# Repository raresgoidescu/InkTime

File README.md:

<!-- Copyright GOIDESCU Rareș-Ștefan 2026 -->

# InkTime

InkTime is a proper solution for the people that can't be bothered to charge their watch daily. This is a beginner's attempt at implementing it. Please see [the disclaimer and the license](#trademark-disclaimer) notice.

## Block Diagram

## Bill of Materials

| Part / Value | Refs | Qty | Procurement | Datasheet |
| :--- | :--- | :---: | :--- | :--- |
| **Active ICs & Semiconductors** | | | | |
| nRF52840-QFAA Microcontroller | U1 | 1 | [DigiKey](https://www.digikey.be/en/products/detail/nordic-semiconductor-asa/NRF52840-QFAA-F-R/15929812) | [DS](https://www.nordicsemi.com/Products/nRF52840) |
| BMA423 Triaxial Accelerometer | IC3 | 1 |[Mouser 262-BMA423](https://eu.mouser.com/ProductDetail/Bosch-Sensortec/BMA423?qs=HXFqYaX1Q2xC%252BSgeGoX3mg%3D%3D) | [DS](https://watchy.sqfmi.com/assets/files/BST-BMA423-DS000-1509600-950150f51058597a6234dd3eaafbb1f0.pdf) |
| BQ25180YBGR Li-Ion Charger | IC1 | 1 |[Mouser 595-BQ25180YBGR](https://eu.mouser.com/ProductDetail/Texas-Instruments/BQ25180YBGR?qs=doiCPypUmgEWjAK%252BJAX6Tw%3D%3D) | [DS](https://www.ti.com/product/BQ25180) |
| DRV2605YZFR Haptic Driver | IC2 | 1 | [Mouser](https://eu.mouser.com/ProductDetail/Texas-Instruments/DRV2605YZFR?qs=9Zb5cNRUa0Ym539PjgFm3g%3D%3D) | [DS](https://www.ti.com/product/DRV2605) |
| MAX17048G+T10 Fuel Gauge | U3 | 1 | [DigiKey](https://www.digikey.com/en/products/detail/analog-devices-inc-maxim-integrated/MAX17048G-T10/3758921) | [DS](https://www.analog.com/en/products/max17048.html) |
| RT6160AWSC Buck-Boost DC-DC | IC9 | 1 |[Mouser 835-RT6160AWSC](https://eu.mouser.com/ProductDetail/Richtek/RT6160AWSC?qs=amGC7iS6iy%2FLd9PSoixZXQ%3D%3D) | [DS](https://www.richtek.com/Products/Switching%20Regulators/Buck-Boost%20Converter/RT6160A) |
| USBLC6-2SC6Y ESD Protection | D3 | 1 | [DigiKey](https://www.digikey.com/en/products/detail/stmicroelectronics/USBLC6-2SC6Y/2819177) | [DS](https://www.st.com/en/protections-and-emi-filters/usblc6-2.html) |
| MBR0530 Schottky Diode | D2, D4, D5 | 3 | [Mouser](https://eu.mouser.com/c/semiconductors/discrete-semiconductors/diodes-rectifiers/schottky-diodes-rectifiers/?m=onsemi&series=MBR0530) | [DS](https://www.onsemi.com/pdf/datasheet/mbr0530t1-d.pdf) |
| DMG2305UX-7 P-CH MOSFET 20V/4.2A | Q1 | 1 | [Mouser](https://ro.mouser.com/ProductDetail/Diodes-Incorporated/DMG2305UX-7?qs=L1DZKBg7t5F%2FNBHrjfxC%252Bg%3D%3D) | [DS](https://www.diodes.com/assets/Datasheets/DMG2305UX.pdf) |
| SI1308EDL-T1-GE3 N-CH MOSFET 30V/1.5A | Q3 | 1 | [Mouser](https://eu.mouser.com/ProductDetail/Vishay-Semiconductors/SI1308EDL-T1-GE3?qs=bX1%252BNvsK%2FBramh9tgpOaEw%3D%3D) |[DS](https://www.vishay.com/docs/63399/si1308edl.pdf) |
| **Connectors & Electromechanical** | | | | |
| 2450AT18B100E 2.45 GHz Antenna | ANT1 | 1 | [Mouser 609-2450AT18B100E](https://www.mouser.co.uk/ProductDetail/Johanson-Technology/2450AT18B100E?qs=yCnrNFeXz%252Bh5MFsFIXGZGA%3D%3D) | [DS](https://www.johansontechnology.com/datasheets/2450AT18B100/2450AT18B100.pdf) |
| 503480-2400 24-pin FPC 0.5 mm | J1 | 1 |[Mouser 538-503480-2400](https://eu.mouser.com/ProductDetail/Molex/503480-2400?qs=OAhjpuo3Vu7efIoxFh9AOw%3D%3D) | [DS](https://www.molex.com/en-us/products/part-detail/5034802400?display=pdf) |
| KH-TYPE-C-16P USB Type-C 16-pin | J4 | 1 | [xonelec.com](https://www.xonelec.com/mpn/kinghelm/khtypec16p) | [DS](https://xonstorage.z8.web.core.windows.net/pdf/kinghelm_khtypec16p_xonjuly20_20_link.pdf) |
| TC2030-IDC 6-pin Debug Adapter | J2 | 1 | [Tag-Connect](https://www.tag-connect.com/product/tc2030-idc-6-pin-tag-connect-plug-of-nails-spring-pin-cable-with-legs) | [DS](https://www.tag-connect.com/wp-content/uploads/bsk-pdf-manager/2019/12/TC2030-IDC-Datasheet-Rev-B.pdf) |
| EVP-AKE31A Tactile Button | SW_DN, SW_ENT, SW_UP | 3 |[Mouser](https://eu.mouser.com/ProductDetail/Panasonic/EVP-AKE31A?qs=EU6FO9ffTwe%252BJzX5LvvHqA%3D%3D) | [DS](https://www.tme.eu/Document/7d6137f818fadb8daa876cedb29b6731/EVPAKseries.pdf) |
| **Inductors** | | | | |
| FTC252012SR47MBCA 0.47 µH | L7 | 1 |[LCSC C5832368](https://www.lcsc.com/product-detail/C5832368.html) | [DS](https://www.lcsc.com/datasheet/C5832368.pdf?spm=wm.sxq.inf.ggs&lcsc_vid=RAVWAlZRTgINBlwCQQJeUgdVT1VdUFFeE1EIVAJWFVYxVlNRQVZcVFJRQFFZUzsOAxUeFF5JWBYZEEoBGA4JCwFIFA4DSA%3D%3D) |
| 744043680 68 µH | L5 | 1 |[Mouser](https://eu.mouser.com/ProductDetail/Wurth-Elektronik/744043680?qs=PGXP4M47uW6VkZq%252BkzjrHA%3D%3D) | [DS](https://www.we-online.com/katalog/datasheet/744043680.pdf) |
| **Passives** | | | | |
| 12 pF 0201 (HFXO/LFXO load caps) | C1, C2, C17, C18 | 4 | Generic 0201 | - |
| 100 nF 0201 decoupling | C5, C7, C8, C12, C19 | 5 | Generic 0201 | - |
| 1 µF 0201[GRM011R60J152KE01L](https://www.snapeda.com/parts/GRM011R60J152KE01L/Murata/view-part/) | C29–C32, C37, C38 | 6 | Murata / Mouser | - |
| 0.1 µF 0201[GRM011R60J152KE01L](https://www.snapeda.com/parts/GRM011R60J152KE01L/Murata/view-part/) | C23, C27, C34, C42 | 4 | Murata / Mouser | - |
| 10 µF 0402 | C24, C39, C1-EP-DR | 3 | Generic 0402 | - |
| 22 µF 0402 | C25, C33 | 2 | Generic 0402 | - |
| 1 µF/50V 0402 (EPD drive) | EPD_C1/2/6–12 | 9 | Generic 0402 | - |
| 3.3 kΩ 0201 (I2C pull-ups) | R17, R18 | 2 | Generic 0201 | - |
| 5.1 kΩ 0201 (USB CC) | R1_USB, R2_USB | 2 | Generic 0201 | - |
| 10 kΩ 0201 (button pull-ups, misc) | R5, R7, R8, R9, R2_EP_DR, R_PWR_EPD | 6 | Generic 0201 | - |
| 0 Ω 0201 (DNP jumpers) | R2, R3, R4 | 3 | Generic 0201 | - |

## Hardware Description

### Power Management

**BQ25180YBGR** charges the LiPo from USB (5V). `PMIC_INT` alerts the MCU to faults and status changes. Q1 provides reverse-polarity protection on the VBUS path.

**RT6160AWSC** generates the 3V3 rail via a buck-boost topology, required because battery voltage (3V–4V2) straddles the 3V3 output. Switching node uses an inductor; output is filtered by capacitors. Controlled via I2C and a GPIO enable pin.

**MAX17048G+T10** estimates battery SoC over I2C using the ModelGauge algorithm, eliminating the need for a power-wasting current-sense resistor. The `ALERT` pin fires when the SoC drops below a configurable threshold.

**MBR0530 diodes** (D2, D4, D5) are arranged to steer power between USB, the battery, and the EPD drive rail to prevent back-feeding across power domains.

### Microcontroller

64 MHz Cortex-M4F, 1 MB Flash, 256 KB RAM, Bluetooth 5.0 LE, USB 2.0 FS. Peripherals used:

- **Power** - The internal DC-DC regulator is enabled via dedicated LC matching to step down the 3V3 rail internally, drastically reducing the active power footprint of the CPU and radio.
- **SPIM3** - E-Paper display (MOSI, SCK + 4 control GPIOs)
- **TWIM0** - shared I2C bus (BMA423, BQ25180, MAX17048, DRV2605, RT6160A)
- **USB** - firmware update / serial via dedicated D+/D− pads through USBLC6 ESD protection
- **RTC0** - timekeeping in sleep, clocked from 32.768 kHz LFXO
- **Radio** - Bluetooth LE for phone time sync

### Clocks

- X1 (32 MHz) - HFXO for CPU and radio. 12 pF load caps C1, C2 placed adjacent.
- X2 (32.768 kHz) - LFXO for RTC. Pins P0.00/XL1 and P0.01/XL2. 12 pF load caps C17, C18.

### Antenna

The 2450AT18B100E chip antenna sits at the board edge with the full copper/trace keep-out zone underneath per the datasheet.
It connects via a matching network.

### Display (SPI)

Molex 503480-2400 24-pin 0.5 mm FPC connector (J1) on the left board edge.
Interface: MOSI, SCK, EPD_CS, EPD_DC, EPD_RST, EPD_BUSY over SPIM3.
The on-board boost drive circuit generates the positive and negative high-voltage rails needed for pixel switching.
SJ1 solder jumper selects the EPD panel variant.

### IMU (I2C)

Step counting, tilt, tap detection, etc.

### Haptics (I2C)

DRV2605YZFR ERM/LRA haptic driver for physical notification feedback.

### Buttons

Three EVP-AKE31A side-entry tactile switches. Debounced via hardware using capacitors (C29–C32 series) and 10 kΩ pull-ups (R5, R7, R8) to ensure clean interrupts waking the MCU from deep sleep.

### Debug Interface

Tag-Connect 6-pin pogo footprint (J2). Signals: SWDIO, SWDCLK, SWO, RESET, VCC, GND.

## nRF52840 Pin Assignment

| Pin | Net | Peripheral | Notes |
| :--- | :--- | :--- | :--- |
| P0.00/XL1 | `XL1` | Crystal X2 | 32.768 kHz LFXO in |
| P0.01/XL2 | `XL2` | Crystal X2 | 32.768 kHz LFXO out |
| XC1, XC2 | `XC1`, `XC2` | Crystal X1 | 32 MHz HFXO |
| P0.06 | `SDA` | IC1, IC2, IC3, U3, IC9 | I2C |
| P0.07 | `SCL` | IC1, IC2, IC3, U3, IC9 | I2C |
| P0.08 | `IMU_INT1` | IMU (BMA421)	Interrupt 1 |
| P0.11	| `PMIC_INT` | LiPo Charger | Fault interrupt |
| P0.12	| `HAPTIC_EN`	| Haptics | Haptics enable |
| P0.13 | `P0.13` | SW_UP | Button |
| P0.14 | `P0.14` | SW_ENT | Button |
| P0.15	| `EPD_DC` | Display D/C |
| P0.16	| `EPD_RST` | Display reset |
| P0.17 | `EPD_BUSY` | Display | Busy status |
| P0.18/RESET | `RESET` | TC2030 J2, pull-up | system reset |
| SWDCLK | `SWDCLK` | TC2030 J2 | SWD clock |
| SWDIO | `SWDIO` | TC2030 J2 | SWD data |
| P1.00 | `SWO` | TP | SWO trace output |
| P1.02 | `P1.02` | SW_DN | Button |
| P1.08 | `IMU_INT2` | IMU | Interrupt 2 |
| P1.10 | `ALERT` | Fuel Gauge | SoC alert |
| D+ | `D+` | USB-C J4 via D3 | USB FS data + |
| D− | `D−` | USB-C J4 via D3 | USB FS data − |
| VBUS | `VBUS` | J4 / R1_USB+R2_USB divider | 5 V bus |
| ANT |	`RF` | 2.4 GHz antenna | Antenna feed |

## Power Consumption Estimates

| Mode | Dominant consumers | Est. current | Battery life (300 mAh) |
| :--- | :--- | ---: | ---: |
| Deep sleep (Static display, BLE off) | nRF52840 RTC + BMA423 sleep + MAX17048 + quiescent ICs | ~120 µA | ~104 days |
| Active (1 EPD refresh/min + BLE adv) | CPU active + Radio TX/RX + EPD boost circuit averaged | ~5–6 mA | ~50 hours |
| Mixed realistic use | Mostly deep sleep, periodic wake on wrist gesture / button press | - | **~7–14 days** |

## Design Logs

- Had to manually approve via in pad overlaps.
- Had to apply neck down to some segments of the power routes, reducing the width to 0.2675 mm (from 0.3 mm).
- Matched lenght for differential lines and symmetric configurations for the crystals.

## PCB Renders

### Top Layer

### Polygon Pours

| Top | Bottom |
|---|---|
|  |  |

| GND | Power |
|---|---|
|  |  |

## Exploded View

## Trademark Disclaimer

This project includes a reproduction of the Viltrumite logo on the PCB silkscreen.

- The Viltrumite logo is trademark of Image Comics and/or its creators.
- This project is non-commercial and is not affiliated with, endorsed by, or sponsored by Image Comics or the Invincible franchise.
- The [CERN-OHL-S v2.0](LICENSE) license governs the electronic design files only and does not grant any rights to the Viltrumite trademark or associated artwork.

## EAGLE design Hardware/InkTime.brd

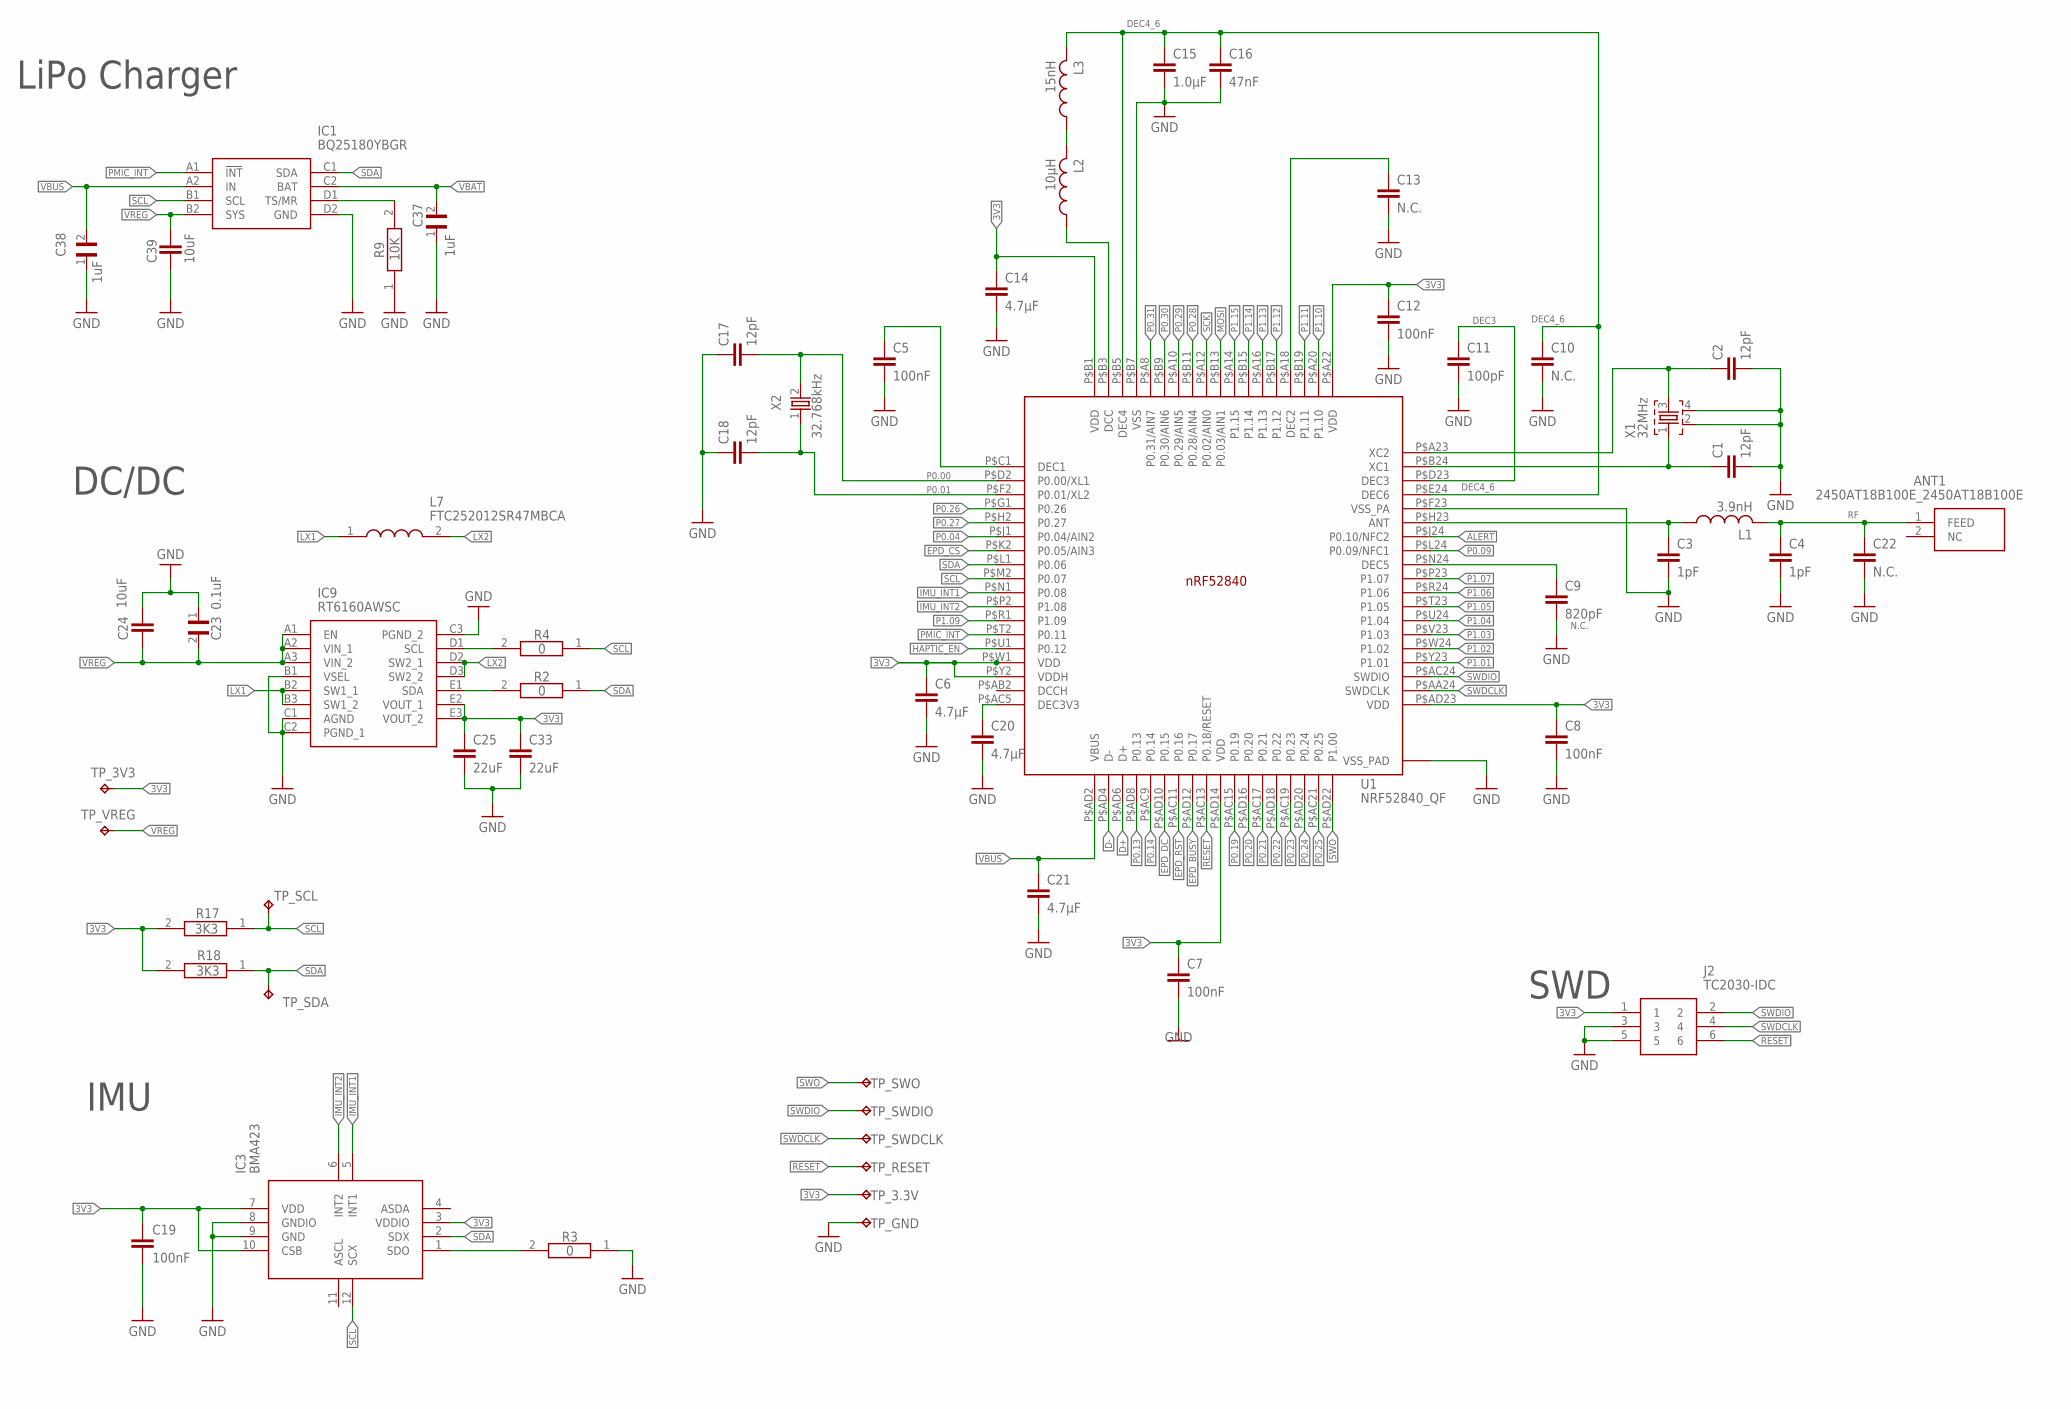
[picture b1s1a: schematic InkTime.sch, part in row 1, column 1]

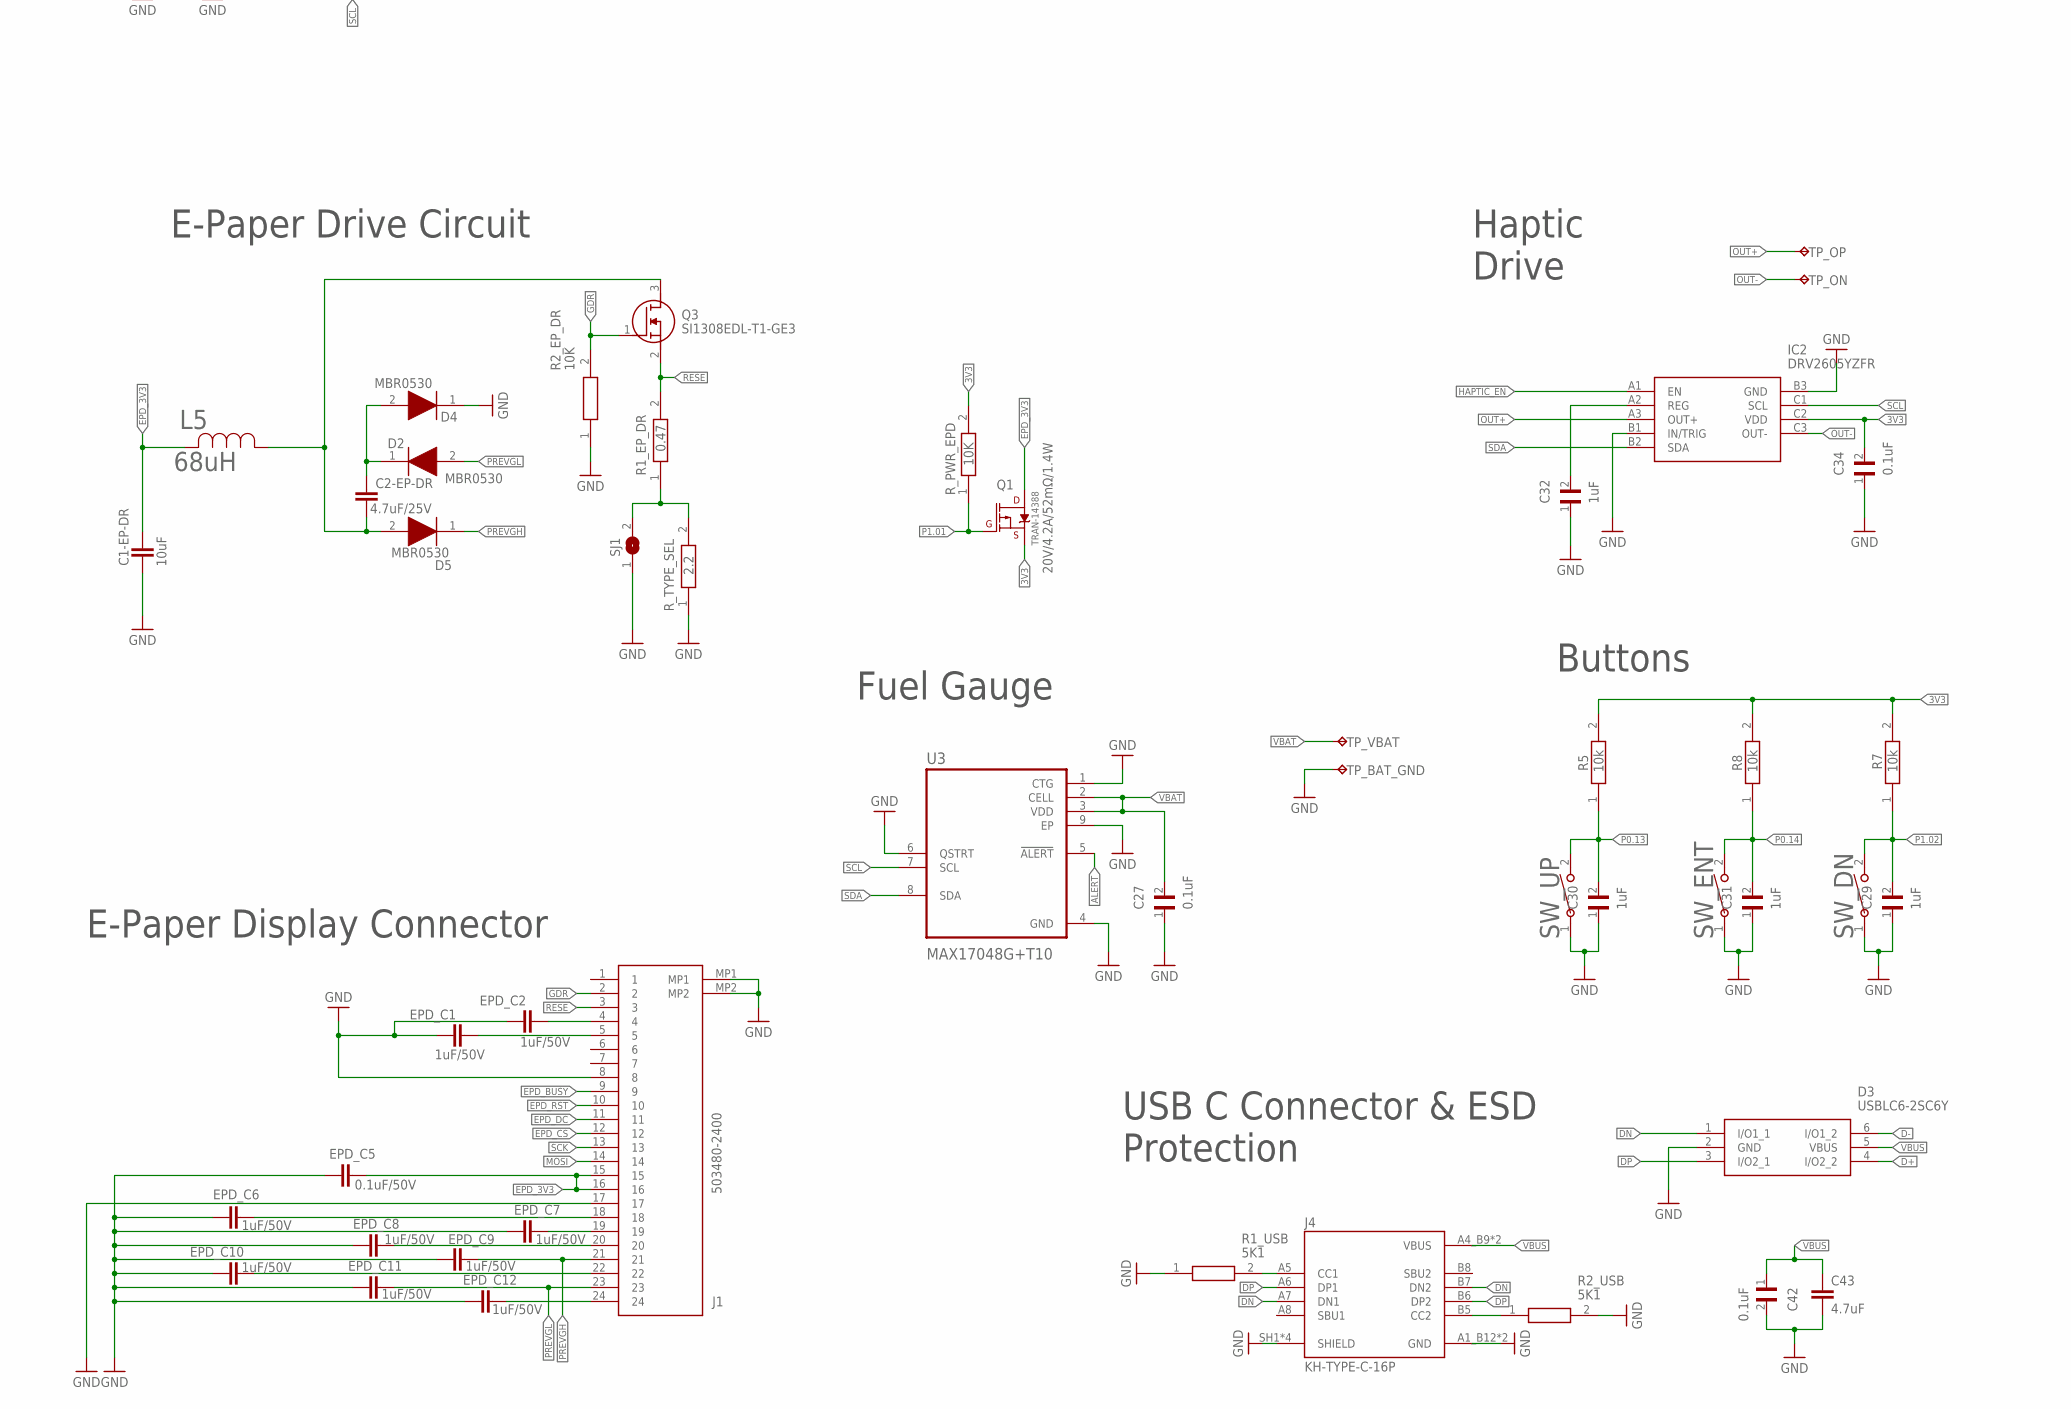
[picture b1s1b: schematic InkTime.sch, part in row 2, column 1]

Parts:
ANT1: 2450AT18B100E_2450AT18B100E; 2450AT18B100E_ANTC3216X140N
C1, C2, C17, C18: 12pF; NORDIC_NRF_3_RESC0201_L
C1-EP-DR, C24, C39: 10uF; NORDIC_NRF_3_RESC0402_L
C2-EP-DR: 4.7uF/25V; NORDIC_NRF_3_RESC0402_L
C3, C4: 1pF; NORDIC_NRF_3_RESC0201_L
C5, C7, C8, C12, C19: 100nF; NORDIC_NRF_3_RESC0201_L
C6, C14, C20, C21: 4.7μF; NORDIC_NRF_3_RESC0402_L
C9: 820pF; NORDIC_NRF_3_RESC0201_L
C10, C13, C22: N.C.; NORDIC_NRF_3_RESC0201_L
C11: 100pF; NORDIC_NRF_3_RESC0201_L
C15: 1.0μF; NORDIC_NRF_3_RESC0402_L
C16: 47nF; NORDIC_NRF_3_RESC0201_L
C23, C27, C34, C42: 0.1uF; GRM011R60J152KE01L_2_CAPC0201X13N
C25, C33: 22uF; NORDIC_NRF_3_RESC0402_L
C29, C30, C31, C32, C37, C38: 1uF; GRM011R60J152KE01L_2_CAPC0201X13N
C43: 4.7uF; NORDIC_NRF_3_RESC0402_L
D2, D4, D5: MBR0530; ESP32_C6_LIBRARY_5_SOD3716X135N
D3: USBLC6-2SC6Y; ESP32_C6_LIBRARY_3_SOT95P280X145-6N
EPD_C1, EPD_C2, EPD_C6, EPD_C7, EPD_C8, EPD_C9, EPD_C10, EPD_C11, EPD_C12: 1uF/50V; NORDIC_NRF_3_RESC0402_L
EPD_C5: 0.1uF/50V; NORDIC_NRF_3_RESC0201_L
IC1: BQ25180YBGR; BQ25180YBGR_BGA8C40P2X4_100X155X50
IC2: DRV2605YZFR; DRV2605YZFR_BGA9C50P3X3_144X144X62
IC3: BMA423; BMA423_BMA423
IC9: RT6160AWSC; RT6160AWSC_BGA15C40P3X5_140X230X60
J1: 503480-2400; 503480-2400_5034802400
J2: TC2030-IDC; TC2030-IDC_TC2030IDC
J4: KH-TYPE-C-16P; KH-TYPE-C-16P_KINGHELM_KH-TYPE-C-16P
L1: 3.9nH; NORDIC_NRF_2_RESC0402_L
L2: 10μH; NORDIC_NRF_2_RESC0402_L
L3: 15nH; NORDIC_NRF_2_RESC0402_L
L5: 68uH; ESP32_C6_LIBRARY_2_IND_4828-WE-TPC_WRE
L7: FTC252012SR47MBCA; MLP2016SR47MT0S1_INDC2016X100N
Q1: 20V/4.2A/52mΩ/1.4W; ESP32_C6_LIBRARY_4_ESP32_C6_LIBRARY_4_ESP32_C6_LIBRARY_4_ES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
Q3: SI1308EDL-T1-GE3; ESP32_C6_LIBRARY_6_SOT65P210X110-3N
R1_EP_DR: 0.47; ERA-1AEB3401C_0201
R1_USB, R2_USB: 5K1; ERA-1AEB3401C_0201
R2, R3, R4: 0; ERA-1AEB3401C_0201
R2_EP_DR, R9: 10K; ERA-1AEB3401C_0201
R5, R7, R8: 10k; ERA-1AEB3401C_0201
R17, R18: 3K3; ERA-1AEB3401C_0201
R_PWR_EPD: 10K; ERA-1AEB3401C_0201
R_TYPE_SEL: 2.2; ERA-1AEB3401C_0201
SJ1: ESP32_C6_LIBRARY_7_JUMPER_SJ
SW_DN: 2025-10-22_07-23-44_LIBRARY_EVP-AKE31ASW_EVP-AKE3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; 2025-10-22_07-23-44_LIBRARY_SW_EVP-AKE31A_PAN
SW_ENT: 2025-10-22_07-23-44_LIBRARY_EVP-AKE31ASW_EVP-AKE3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; 2025-10-22_07-23-44_LIBRARY_SW_EVP-AKE31A_PAN
SW_UP: 2025-10-22_07-23-44_LIBRARY_EVP-AKE31ASW_EVP-AKE3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; 2025-10-22_07-23-44_LIBRARY_SW_EVP-AKE31A_PAN
TP_3.3V, TP_3V3: HECTOR_WATCH_1_TPTP20R; HECTOR_WATCH_1_TP20R
TP_BAT_GND: HECTOR_WATCH_1_TPTP20R; HECTOR_WATCH_1_TP20R
TP_GND: HECTOR_WATCH_1_TPTP20R; HECTOR_WATCH_1_TP20R
TP_ON: HECTOR_WATCH_1_TPTP20R; HECTOR_WATCH_1_TP20R
TP_OP: HECTOR_WATCH_1_TPTP20R; HECTOR_WATCH_1_TP20R
TP_RESET: HECTOR_WATCH_1_TPTP20R; HECTOR_WATCH_1_TP20R
TP_SCL: HECTOR_WATCH_1_TPTP20R; HECTOR_WATCH_1_TP20R
TP_SDA: HECTOR_WATCH_1_TPTP20R; HECTOR_WATCH_1_TP20R
TP_SWDCLK: HECTOR_WATCH_1_TPTP20R; HECTOR_WATCH_1_TP20R
TP_SWDIO: HECTOR_WATCH_1_TPTP20R; HECTOR_WATCH_1_TP20R
TP_SWO: HECTOR_WATCH_1_TPTP20R; HECTOR_WATCH_1_TP20R
TP_VBAT: HECTOR_WATCH_1_TPTP20R; HECTOR_WATCH_1_TP20R
TP_VREG: HECTOR_WATCH_1_TPTP20R; HECTOR_WATCH_1_TP20R
U1: NRF52840_QF; NORDIC_NRF_4_AQFN50P700X700X85_HS-74N
U3: MAX17048G+T10; ESP32_C6_LIBRARY_SON50P200X200X80-9N
X1: 32MHz; NORDIC_NRF_BT-XTAL_2016_N
X2: 32.768kHz; NORDIC_NRF_1_XTAL_3215_N

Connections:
3V3: C6.1, C7.1, C8.1, C12.1, C14.1, C19.2, C25.1, C33.1, C34.2, IC2.C2 (VDD), IC3.3 (VDDIO), IC3.7 (VDD), IC3.10 (CSB), IC9.E2 (VOUT_1), IC9.E3 (VOUT_2), J2.1, Q1.2 (S), R5.2, R7.2, R8.2, R17.2, R18.2, R_PWR_EPD.2, TP_3.3V.TP, TP_3V3.TP, U1.P$A22 (VDD), U1.P$AD14 (VDD), U1.P$AD23 (VDD), U1.P$B1 (VDD), U1.P$W1 (VDD), U1.P$Y2 (VDDH)
ALERT: U1.P$J24 (P0.10/NFC2), U3.5 (!ALERT)
D+: D3.4 (I/O2_2), U1.P$AD6 (D+)
D-: D3.6 (I/O1_2), U1.P$AD4 (D-)
DEC3: C11.1, U1.P$D23 (DEC3)
DEC4_6: C10.1, C15.1, C16.1, L3.2, U1.P$B5 (DEC4), U1.P$E24 (DEC6)
DN: D3.1 (I/O1_1), J4.A7 (DN1), J4.B7 (DN2)
DP: D3.3 (I/O2_1), J4.A6 (DP1), J4.B6 (DP2)
EPD_3V3: C1-EP-DR.1, EPD_C5.2, J1.15, J1.16, L5.2, Q1.3 (D)
EPD_BUSY: J1.9, U1.P$AD12 (P0.17)
EPD_CS: J1.12, U1.P$K2 (P0.05/AIN3)
EPD_DC: J1.11, U1.P$AD10 (P0.15)
EPD_RST: J1.10, U1.P$AC11 (P0.16)
GDR: J1.2, Q3.1 (G), R2_EP_DR.2
GND: C1.2, C1-EP-DR.2, C2.2, C3.2, C4.2, C5.2, C6.2, C7.2, C8.2, C9.2, C10.2, C11.2, C12.2, C13.2, C14.2, C15.2, C16.2, C17.1, C18.1, C19.1, C20.2, C21.2, C22.2, C23.1, C24.1, C25.2, C27.1, C29.1, C30.1, C31.1, C32.1, C33.2, C34.1, C37.1, C38.1, C39.2, C42.2, C43.2, D3.2 (GND), D4.1 (K), EPD_C1.1, EPD_C2.1, EPD_C5.1, EPD_C6.1, EPD_C7.1, EPD_C8.1, EPD_C9.1, EPD_C10.1, EPD_C11.1, EPD_C12.1, IC1.D2 (GND), IC2.B1 (IN/TRIG), IC2.B3 (GND), IC3.8 (GNDIO), IC3.9 (GND), IC9.B1 (VSEL), IC9.C1 (AGND), IC9.C2 (PGND_1), IC9.C3 (PGND_2), J1.8, J1.17, J1.MP1, J1.MP2, J2.3, J2.5, J4.A1_B12 (GND), J4.A12_B1 (GND), J4.SH1 (SHIELD), J4.SH2 (SHIELD), J4.SH3 (SHIELD), J4.SH4 (SHIELD), R1_USB.1, R2_EP_DR.1, R2_USB.2, R3.1, R9.1, R_TYPE_SEL.1, SJ1.1, SW_DN.1, SW_ENT.1, SW_UP.1, TP_BAT_GND.TP, TP_GND.TP, U1.P$74 (VSS_PAD), U1.P$75 (VSS_PAD), U1.P$76 (VSS_PAD), U1.P$77 (VSS_PAD), U1.P$78 (VSS_PAD), U1.P$79 (VSS_PAD), U1.P$80 (VSS_PAD), U1.P$81 (VSS_PAD), U1.P$82 (VSS_PAD), U1.P$83 (VSS_PAD), U1.P$84 (VSS_PAD), U1.P$85 (VSS_PAD), U1.P$86 (VSS_PAD), U1.P$87 (VSS_PAD), U1.P$88 (VSS_PAD), U1.P$89 (VSS_PAD), U1.P$90 (VSS_PAD), U1.P$B7 (VSS), U1.P$F23 (VSS_PA), U3.1 (CTG), U3.4 (GND), U3.6 (QSTRT), U3.9 (EP), X1.2, X1.4
HAPTIC_EN: IC2.A1 (EN), U1.P$U1 (P0.12)
IMU_INT1: IC3.5 (INT1), U1.P$N1 (P0.08)
IMU_INT2: IC3.6 (INT2), U1.P$P2 (P1.08)
LX1: IC9.B2 (SW1_1), IC9.B3 (SW1_2), L7.1
LX2: IC9.D2 (SW2_1), IC9.D3 (SW2_2), L7.2
MOSI: J1.14, U1.P$B13 (P0.03/AIN1)
unnamed: C5.1, U1.P$C1 (DEC1)
unnamed: C3.1, L1.1, U1.P$H23 (ANT)
unnamed: C20.1, U1.P$AC5 (DEC3V3)
unnamed: IC1.D1 (TS/MR), R9.2
unnamed: C2-EP-DR.2, D5.2 (A), L5.1, Q3.3 (D)
unnamed: C2-EP-DR.1, D2.1 (K), D4.2 (A)
unnamed: IC9.D1 (SCL), R4.2
unnamed: IC9.E1 (SDA), R2.2
unnamed: IC3.1 (SDO), R3.2
unnamed: J4.A5 (CC1), R1_USB.2
unnamed: EPD_C2.2, J1.4
unnamed: EPD_C1.2, J1.5
unnamed: R1_EP_DR.1, R_TYPE_SEL.2, SJ1.2
unnamed: J4.B5 (CC2), R2_USB.1
unnamed: C32.2, IC2.A2 (REG)
unnamed: EPD_C6.2, J1.18
unnamed: EPD_C7.2, J1.19
unnamed: EPD_C8.2, J1.20
unnamed: EPD_C10.2, J1.22
unnamed: EPD_C12.2, J1.24
unnamed: C9.1, U1.P$N24 (DEC5)
unnamed: C1.1, U1.P$B24 (XC1), X1.1
unnamed: C2.1, U1.P$A23 (XC2), X1.3
unnamed: C13.1, U1.P$A18 (DEC2)
unnamed: L2.2, L3.1
unnamed: L2.1, U1.P$B3 (DCC)
OUT+: IC2.A3 (OUT+), TP_OP.TP
OUT-: IC2.C3 (OUT-), TP_ON.TP
P0.00: C17.2, U1.P$D2 (P0.00/XL1), X2.2
P0.01: C18.2, U1.P$F2 (P0.01/XL2), X2.1
P0.04: U1.P$J1 (P0.04/AIN2)
P0.09: U1.P$L24 (P0.09/NFC1)
P0.13: C30.2, R5.1, SW_UP.2, U1.P$AD8 (P0.13)
P0.14: C31.2, R8.1, SW_ENT.2, U1.P$AC9 (P0.14)
P0.19: U1.P$AC15 (P0.19)
P0.20: U1.P$AD16 (P0.20)
P0.21: U1.P$AC17 (P0.21)
P0.22: U1.P$AD18 (P0.22)
P0.23: U1.P$AC19 (P0.23)
P0.24: U1.P$AD20 (P0.24)
P0.25: U1.P$AC21 (P0.25)
P0.26: U1.P$G1 (P0.26)
P0.27: U1.P$H2 (P0.27)
P0.28: U1.P$B11 (P0.28/AIN4)
P0.29: U1.P$A10 (P0.29/AIN5)
P0.30: U1.P$B9 (P0.30/AIN6)
P0.31: U1.P$A8 (P0.31/AIN7)
P1.01: Q1.1 (G), R_PWR_EPD.1, U1.P$Y23 (P1.01)
P1.02: C29.2, R7.1, SW_DN.2, U1.P$W24 (P1.02)
P1.03: U1.P$V23 (P1.03)
P1.04: U1.P$U24 (P1.04)
P1.05: U1.P$T23 (P1.05)
P1.06: U1.P$R24 (P1.06)
P1.07: U1.P$P23 (P1.07)
P1.09: U1.P$R1 (P1.09)
P1.10: U1.P$A20 (P1.10)
P1.11: U1.P$B19 (P1.11)
P1.12: U1.P$B17 (P1.12)
P1.13: U1.P$A16 (P1.13)
P1.14: U1.P$B15 (P1.14)
P1.15: U1.P$A14 (P1.15)
PMIC_INT: IC1.A1 (!INT), U1.P$T2 (P0.11)
PREVGH: D5.1 (K), EPD_C9.2, J1.21
PREVGL: D2.2 (A), EPD_C11.2, J1.23
RESE: J1.3, Q3.2 (S), R1_EP_DR.2
RESET: J2.6, TP_RESET.TP, U1.P$AC13 (P0.18/RESET)
RF: ANT1.1 (FEED), C4.1, C22.1, L1.2
SCK: J1.13, U1.P$A12 (P0.02/AIN0)
SCL: IC1.B1 (SCL), IC2.C1 (SCL), IC3.12 (SCX), R4.1, R17.1, TP_SCL.TP, U1.P$M2 (P0.07), U3.7 (SCL)
SDA: IC1.C1 (SDA), IC2.B2 (SDA), IC3.2 (SDX), R2.1, R18.1, TP_SDA.TP, U1.P$L1 (P0.06), U3.8 (SDA)
SWDCLK: J2.4, TP_SWDCLK.TP, U1.P$AA24 (SWDCLK)
SWDIO: J2.2, TP_SWDIO.TP, U1.P$AC24 (SWDIO)
SWO: TP_SWO.TP, U1.P$AD22 (P1.00)
VBAT: C27.2, C37.2, IC1.C2 (BAT), TP_VBAT.TP, U3.2 (CELL), U3.3 (VDD)
VBUS: C21.1, C38.2, C42.1, C43.1, D3.5 (VBUS), IC1.A2 (IN), J4.A4_B9 (VBUS), J4.A9_B4 (VBUS), U1.P$AD2 (VBUS)
VREG: C23.2, C24.2, C39.1, IC1.B2 (SYS), IC9.A1 (EN), IC9.A2 (VIN_1), IC9.A3 (VIN_2), TP_VREG.TP

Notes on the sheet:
LiPo Charger
DC/DC
IMU
SWD
E-Paper Drive Circuit
E-Paper Display Connector
Fuel Gauge
Haptic Drive
Buttons
USB C Connector & ESD Protection

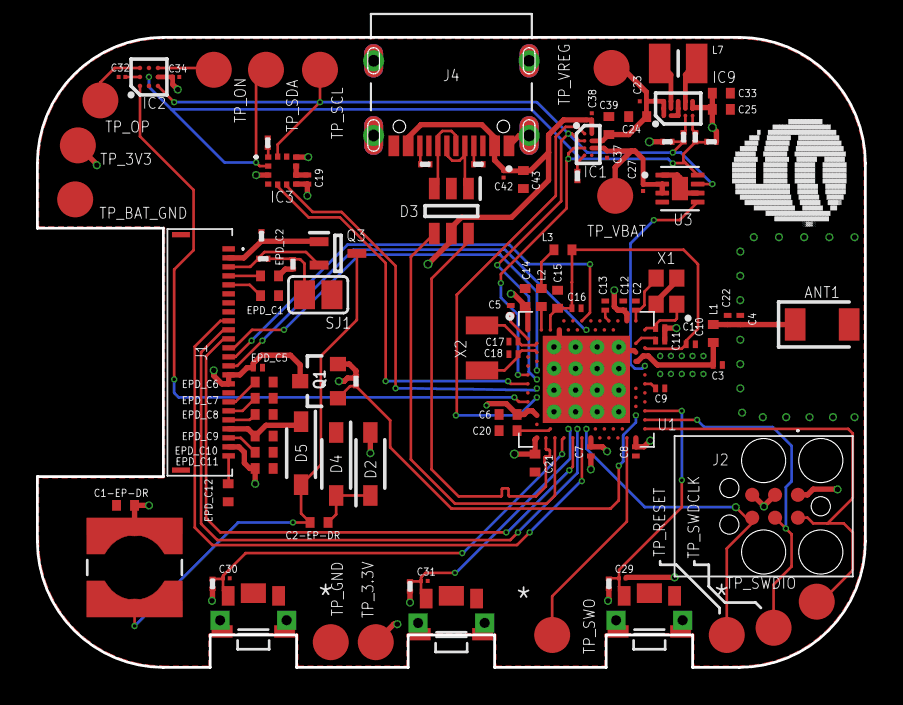
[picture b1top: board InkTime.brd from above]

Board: 4 copper layers, 46.0 x 35.0 mm, 105 parts (0 on the bottom side), 70 nets.

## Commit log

2026-04-21 Add Readme, needa update board
2026-04-21 images and readme update
2026-04-21 hardware/
2026-04-21 mechanical and manufacturing

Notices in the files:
parts and their libraries:
COPYRIGHT: Copyright (C) 2024 Ultra Librarian. All rights reserved.
COPYRIGHT: Copyright (C) 2025 Ultra Librarian. All rights reserved.
